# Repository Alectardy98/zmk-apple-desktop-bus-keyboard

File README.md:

# ⌨️ Apple Desktop Bus QMK/VIAL Fork by Alectardy98

**This Fork includes all source code and compiled assets to create a modified Apple Desktop Bus controller using an RP2040 to function with Vial remapping software. All credit to the original source by Matt Chesters**

One change has been made to the files provided from the photo shown above. The USB-C port has been moved to the bottom side for parity with the 3D models provided by Matt Chesters

Ordering Instructions:
Inside the repo, you will find a folder called "Production_Files_JLCPCB"
On JLCPCB, you will want to upload the GERBER-ADBv2.zip
At the bottom, you can choose to assemble components on either the top side or both sides. It is recommended to assemble both sides for a no-solder solution for the USB port. If you choose to assemble the top only to save money in production, you can instead use the JST connection in tandem with a universal daughterboard.

When selecting parts, you may see a duplicate part error; you can just acknowledge that both locations share the same part.

When the PCB arrives, you can decide to use the pre-compiled firmware called alectardy98_adbkal_vial.uf2
When you initially plug the board into your computer, you will see a new USB device. You simply need to drag and drop the file into the root of that drive. Once the firmware is finished flashing, it should auto-eject, and you should be good to go

## ✍️ Aknolagments
This project was only made possible due to contributions made by magic_shiba

## ⚠️ Disclaimer
This project has been verified as operational by Alectardy98; the new revision with USB-C flipped to the bottom side of the PCB has not been ordered or tested. This software is released without guarantee.

# All information below is from the original creator, Matt Chesters
.
.
.

# ⌨️ Apple Desktop Bus Keyboard modernization project

**This repository includes all the files used in the [mtt](https://www.youtube.com/@mttcx) YouTube video, _"[Apple's BEST keyboard... reimagined](https://www.youtube.com/watch?v=NW_LLVD3R3c)"_.**

<blockquote>
The 1986 Apple Desktop Bus Keyboard is a design marvel known for its enjoyable typing experience, but using it today requires some engineering. This modernization project introduces a custom PCB and development board to add Bluetooth connectivity using ZMK, a low-energy display for layer and device status, and a rotary encoder for volume control. 
</blockquote>

##

This README can be used as supporting information to the video. If you are undertaking this project yourself, please familiarize yourself with [ZMK firmware](https://zmk.dev), and the PCB design and schematic files.

## ⚠️ Disclaimer
The results will vary depending on the condition of your keyboard.  
While efforts have been made to create a functional project, variations in individual keyboard conditions may lead to unique issues.

## ✍️ Schematic & Design
The PCB was designed in KiCad 8.0.

The Schematic, Design, and component Footprints are included in the [KiCad project files](./assets/kicad). 

If you are working on this project, take the time to thoroughly review the design and schematic to understand PCB utilization.

## 🛒 Bill of Materials

| Description | Part | Quantity | Link |
|---|---|---|---|
| Development Board | Seeed Studio XIAO nRF52840 | 1 | [Seeed Studio](https://wiki.seeedstudio.com/XIAO_BLE/) |
| Display | nice!view | 1 | [nice!](https://nicekeyboards.com/nice-view) |
| Rotary encoder | EC11 | 1 | [Amazon](https://www.amazon.co.uk/gp/product/B08728PS6N/ref=ppx_yo_dt_b_search_asin_title?ie=UTF8&psc=1)
| USB Port | USB TYPE-C 6P | 1 | [LCSC Electronics](https://www.lcsc.com/product-detail/USB-Connectors_SHOU-HAN-TYPE-C-6P-QT073_C2681548.html/)|
| Display/Encoder receptacle | JST SM05B | 2 | [LCSC Electronics](https://www.lcsc.com/product-detail/Wire-To-Board-Connector_JST-SM05B-SRSS-TB-LF-SN_C136657.html)|
| Display/Encoder plug | JST SHR-05V-S-B | 2 | [See below](#display%20&amp;%20encoder%20cables)|
| Lithium Polymer Battery | 110mAh | 1 | [Cool Components](https://coolcomponents.co.uk/products/lithium-polymer-battery-110mah?_pos=1&_psq=110mw&_ss=e&_v=1.0)
| Battery Connector | JST S2B-PH | 1 | [LCSC Electronics](https://www.lcsc.com/product-detail/Wire-To-Board-Connector_JST-S2B-PH-K-S-GW_C157932.html)|
| 10k resistor | 10k 0805 | 4 | [LCSC Electronics](https://www.lcsc.com/product-detail/Chip-Resistor-Surface-Mount_UNI-ROYAL-Uniroyal-Elec-0805W8F1002T5E_C17414.html)|
| 5.1k resistor | 5.1k 0805 | 2 | [LCSC Electronics](https://www.lcsc.com/product-detail/Chip-Resistor-Surface-Mount_UNI-ROYAL-Uniroyal-Elec-0805W8F5101T5E_C27834.html)|
| Power switch | MINI MSK12CO2 | 1 | [LCSC Electronics](https://www.lcsc.com/product-detail/Slide-Switches_SHOU-HAN-MINI-MSK12CO2_C2681570.html)

## 🔌 Display & encoder cables
As the small JST connectors used to connect the PCB to the display and rotary encoder requires specialist crimping tools, I opted to have the two cables fabricated by [LCSC custom cables](https://www.lcsc.com/customcables/), to the following specification:

| LCSC Part | Manufacture Part | Quantity |
|---|---|---|
| C268102 | JST SHR-05V-S-B | 1 |
| C263995 | SSH-003T-P0.2-H | 5 |

* Cable: AWG 30
* Length: 300mm
* Side 1: JST Connector
* Side 2: Flat cut wires

## 🛍️ Ordering the PCB
For convenience, the Production files have been included in this repository. These can be used to order your own PCB from a prototyping company, such as JLCPCB or PCBWay.

Please be comfortable with the ordering and validation process, as each company is different and may have inaccuracies you are responsible for.

1. Upload the [./assets/pcb/production-packed.zip]() to a provider.
2. If using the Assembly services, make sure all components are correctly placed.

## 📸 Flashing the XIAO Dev Board with ZMK
If you want to modify the firmware, you can review the code in [./boards/shields/adbk]() following the guidance from [ZMK documentation](https://zmk.dev/docs/development/hardware-integration/new-shield).

I have added a release with the firmware I use daily.

1. Connect the XIAO to your computer.
2. Download the **adbk_fw.uf2** from the [Releases](https://github.com/mattchesters/zmk-apple-desktop-bus-keyboard/releases/).
3. Place the XIAO nRF52840 in [bootloader mode](https://wiki.seeedstudio.com/XIAO_BLE/).
4. Drag and drop the **adbk_fw.uf2** file to the **XIAO-SENSE** volume on your computer.

The board will automatically exit bootloader mode and is ready to use.

## 🧑‍🏭 Preparing the PCB
If you have ordered from a fabrication company with assembly services, the may only have to solder the XIAO nRF52840 and through-hole component.

Review the schematic and design files to understand how the components are placed on the PCB.

## 🪛 Preparing the Keyboard
To install the custom components, some parts need to be removed. The process is reversible, allowing the keyboard to be restored to its original state.

1. Flip over the keyboard and remove the 3x screws with a PH2 driver bit.
2. Holding the top of the keyboard, return it to the upright position, then remove the top casing by lifting it upwards.
3. Carefully remove the 20 pin DIP package by lifting each side with equal force.
4. Remove the board from the PCB, by lift the top, and then sliding it upwards.
5. Desolder and remove the ADB ports.
6. Store the ADB ports and 20-pin DIP package in anti-static packaging for preservation.

## 🖨️ 3D Printed parts
The following parts help facilitate the modifications. These are:
* [Power button with Display cutout](./assets/models/power-cap)
* [ADB Port with switch and USB-C cutout](./assets/models/usb)
* [ADB Port with EC11 cutout](./assets/models/encoder)
* [EC11 encoder knob]((./assets/models/encoder))

These files are provided in STEP and 3MF formats.  
STEP allows for accurate modification in CAD software.  
3MF is designed to be more accessible for 3D printing.

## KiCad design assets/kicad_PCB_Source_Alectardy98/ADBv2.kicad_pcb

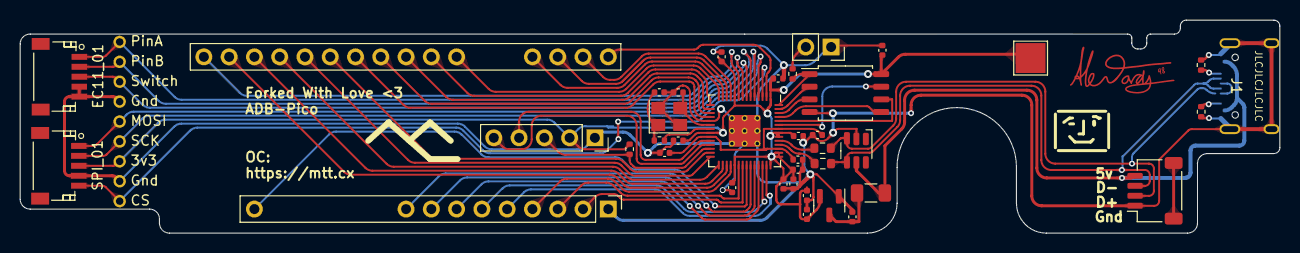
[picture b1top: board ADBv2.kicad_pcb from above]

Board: 2 copper layers, 126.6 x 21.4 mm, 49 parts (1 on the bottom side), 54 nets.

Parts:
C2, C3: 22pF; C_0402_1005Metric
C4, C6, C7, C11: 1uF; C_0402_1005Metric
C5, C8, C9, C12, C13, C14, C15, C16, C17, C18: 100nF; C_0402_1005Metric
C10: 10uF; C_0402_1005Metric
EC11_01: EC11; CONN-SMD_SM05B-SRSS-TB-LF-SN
F1: 500mA; Fuse_1206_3216Metric
H1, H2, H3, H4, H5, H6, H7, H9, H10: Tht; Small THT
H8: Random Hole; Alectardy985
J2: TOP; PinHeader_1x20_P2.54mm_Vertical
J3: BOTTOM; PinHeader_1x20_P2.54mm_Vertical
J5: USB_C; USB_C_Receptacle_HRO_TYPE-C-31-M-12
J6: Conn_01x04_MountingPin; JST_SH_SM04B-SRSS-TB_1x04-1MP_P1.00mm_Horizontal
J20: SWD; PinSocket_1x05_P2.54mm_Vertical
R6, R12: 5.1k; R_0402_1005Metric
R7: 10k; R_0402_1005Metric
R8, R9: 27R; R_0603_1608Metric
R10, R11: 1k; R_0402_1005Metric
SPI_01: SPI; CONN-SMD_SM05B-SRSS-TB-LF-SN
SW2: Boot; PinSocket_1x02_P2.54mm_Vertical
U2: RP2040; RP2040-QFN-56
U3: SRV05-4; SOT-23-6-routable
U5: XC6206; SOT-23
U6: W25Q128JVS; SOIC-8_5.23x5.23mm_P1.27mm
V+1: 3v3Pad; TestPoint_Pad_3.0x3.0mm
Y1: 12MHz; Crystal_SMD_3225-4Pin_3.2x2.5mm

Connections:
+1V1: C7.1, C8.1, C9.1, U2.23 (DVDD), U2.45 (VREG_VOUT), U2.50 (DVDD)
+3V3: C5.1, C6.2, C10.1, C11.1, C12.1, C13.1, C14.1, C15.1, C16.1, C17.1, C18.1, H3.1 (Pin_1_1), J20.2, R7.1, SPI_01.3, U2.1 (IOVDD), U2.10 (IOVDD), U2.22 (IOVDD), U2.33 (IOVDD), U2.42 (IOVDD), U2.43 (ADC_AVDD), U2.44 (VREG_VIN), U2.48 (USB_VDD), U2.49 (IOVDD), U5.2 (VO), U6.8 (VCC), V+1.1 (Pin_1_1)
+5V: C4.2, F1.2, U5.3 (VI)
/CC1: J5.A5 (CC1), R6.1
/CC2: J5.B5 (CC2), R12.1
/D_+: R8.2, U2.47 (D+)
/D_-: R9.2, U2.46 (D-)
/XTAL_O: C3.2, R10.1, Y1.1
/~USB_BOOT: R11.1, SW2.2
C0: J3.2 (C0), U2.35 (GPIO23)
C1: J3.3 (C1), U2.34 (GPIO22)
C2: J3.4 (C2), U2.32 (GPIO21)
C3: J3.5 (C3), U2.41 (GPIO29/ADC3)
C4: J3.6 (C4), U2.40 (GPIO28/ADC2)
C5: J3.7 (C5), U2.39 (GPIO27/ADC1)
C6: J3.8 (C6), U2.38 (GPIO26/ADC0)
C7: J3.9 (C7), U2.37 (GPIO25)
CS: R11.2, U2.56 (QSPI_SS_N), U6.1 (~CS)
CS1: H1.1 (Pin_1_1), SPI_01.5, U2.3 (GPIO1)
CapsLock: J3.15 (CAPSLOCK), U2.36 (GPIO24)
Command: J2.4 (COMMAND), U2.13 (GPIO10)
Control: J2.16 (CONTROL), U2.31 (GPIO20)
DBUS+: J5.A6 (D+), J5.B6 (D+), J6.2, R8.1, U3.3 (IO2)
DBUS-: J5.A7 (D-), J5.B7 (D-), J6.3, R9.1, U3.4 (IO3)
EC11Pin1: EC11_01.1, H9.1 (Pin_1_1), U2.8 (GPIO6)
EC11Pin2: EC11_01.2, H7.1 (Pin_1_1), U2.7 (GPIO5)
EC11Pin3: EC11_01.3, H6.1 (Pin_1_1), U2.6 (GPIO4)
GND: C2.1, C3.1, C4.1, C5.2, C6.1, C7.2, C8.2, C9.2, C10.2, C11.2, C12.2, C13.2, C14.2, C15.2, C16.2, C17.2, C18.2, EC11_01.4, EC11_01.5, H2.1 (Pin_1_1), H10.1 (Pin_1_1), J3.1 (GROUND), J5.A1 (GND), J5.A12 (GND), J5.B1 (GND), J5.B12 (GND), J5.S1 (SHIELD), J6.1, J20.1, R6.2, R12.2, SPI_01.4, SW2.1, U2.19 (TESTEN), U2.57 (GND), U3.2 (VN), U5.1 (GND), U6.4 (GND), Y1.2, Y1.4
MOSI: H5.1 (Pin_1_1), SPI_01.1, U2.5 (GPIO3)
unnamed: C2.2, U2.20 (XTAL_IN), Y1.3
unnamed: R10.2, U2.21 (XTAL_OUT)
Option: J2.3 (OPTION), U2.12 (GPIO9)
Power: J2.15 (POWER), U2.30 (GPIO19)
QSPI_CLK: U2.52 (QSPI_SCLK), U6.6 (CLK)
R0: J2.11 (R0), U2.18 (GPIO15)
R1: J2.2 (R1), U2.11 (GPIO8)
R2: J2.1 (R2), U2.2 (GPIO0)
R3: J2.13 (R3), U2.28 (GPIO17)
R4: J2.7 (R4), U2.14 (GPIO11)
R5: J2.8 (R5), U2.15 (GPIO12)
R6: J2.9 (R6), U2.16 (GPIO13)
R7: J2.10 (R7), U2.17 (GPIO14)
R8: J2.12 (R8), U2.27 (GPIO16)
R9: J2.14 (R9), U2.29 (GPIO18)
SCK: H4.1 (Pin_1_1), SPI_01.2, U2.4 (GPIO2)
SD0: U2.53 (QSPI_SD0), U6.5 (DI(IO0))
SD1: U2.55 (QSPI_SD1), U6.2 (DO(IO1))
SD2: U2.54 (QSPI_SD2), U6.3 (IO2)
SD3: U2.51 (QSPI_SD3), U6.7 (IO3)
SWCLK: J20.4, U2.24 (SWCLK)
SWD: J20.5, U2.25 (SWDIO)
Shift: J2.17 (SHIFT), U2.9 (GPIO7)
VBUS: F1.1, J5.A4 (VBUS), J5.A9 (VBUS), J5.B4 (VBUS), J5.B9 (VBUS), J6.4, U3.5 (VP)
~RESET: J20.3, R7.2, U2.26 (~RUN)
